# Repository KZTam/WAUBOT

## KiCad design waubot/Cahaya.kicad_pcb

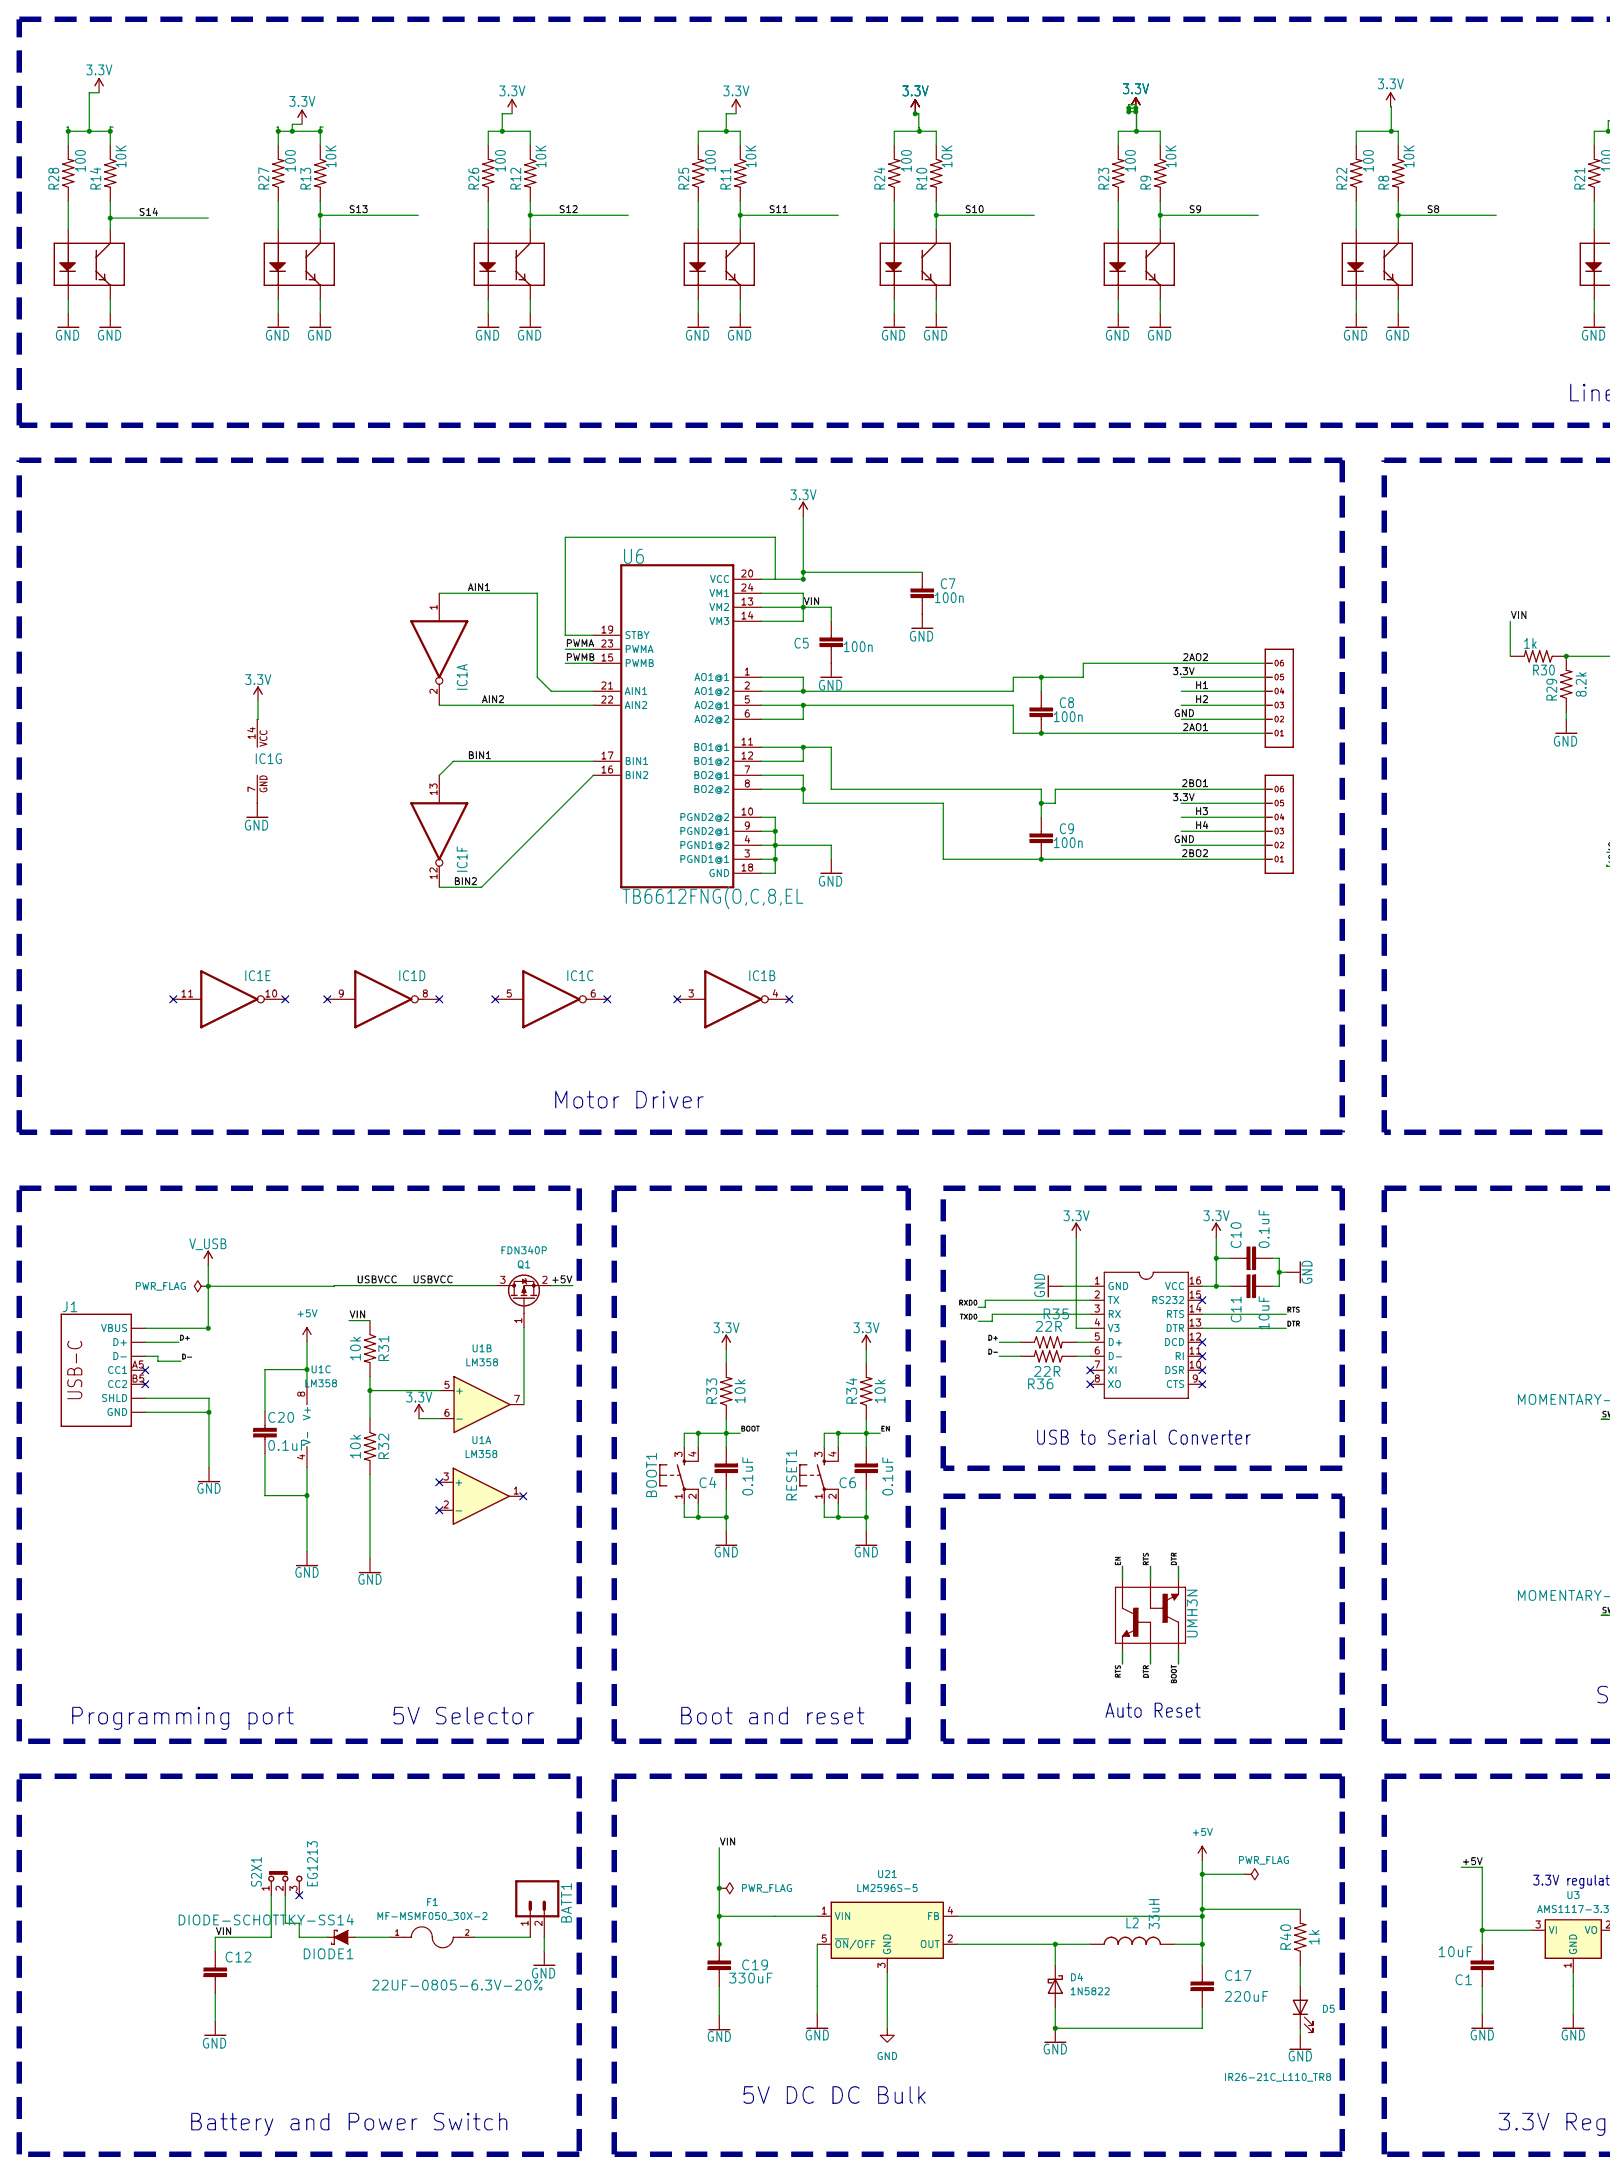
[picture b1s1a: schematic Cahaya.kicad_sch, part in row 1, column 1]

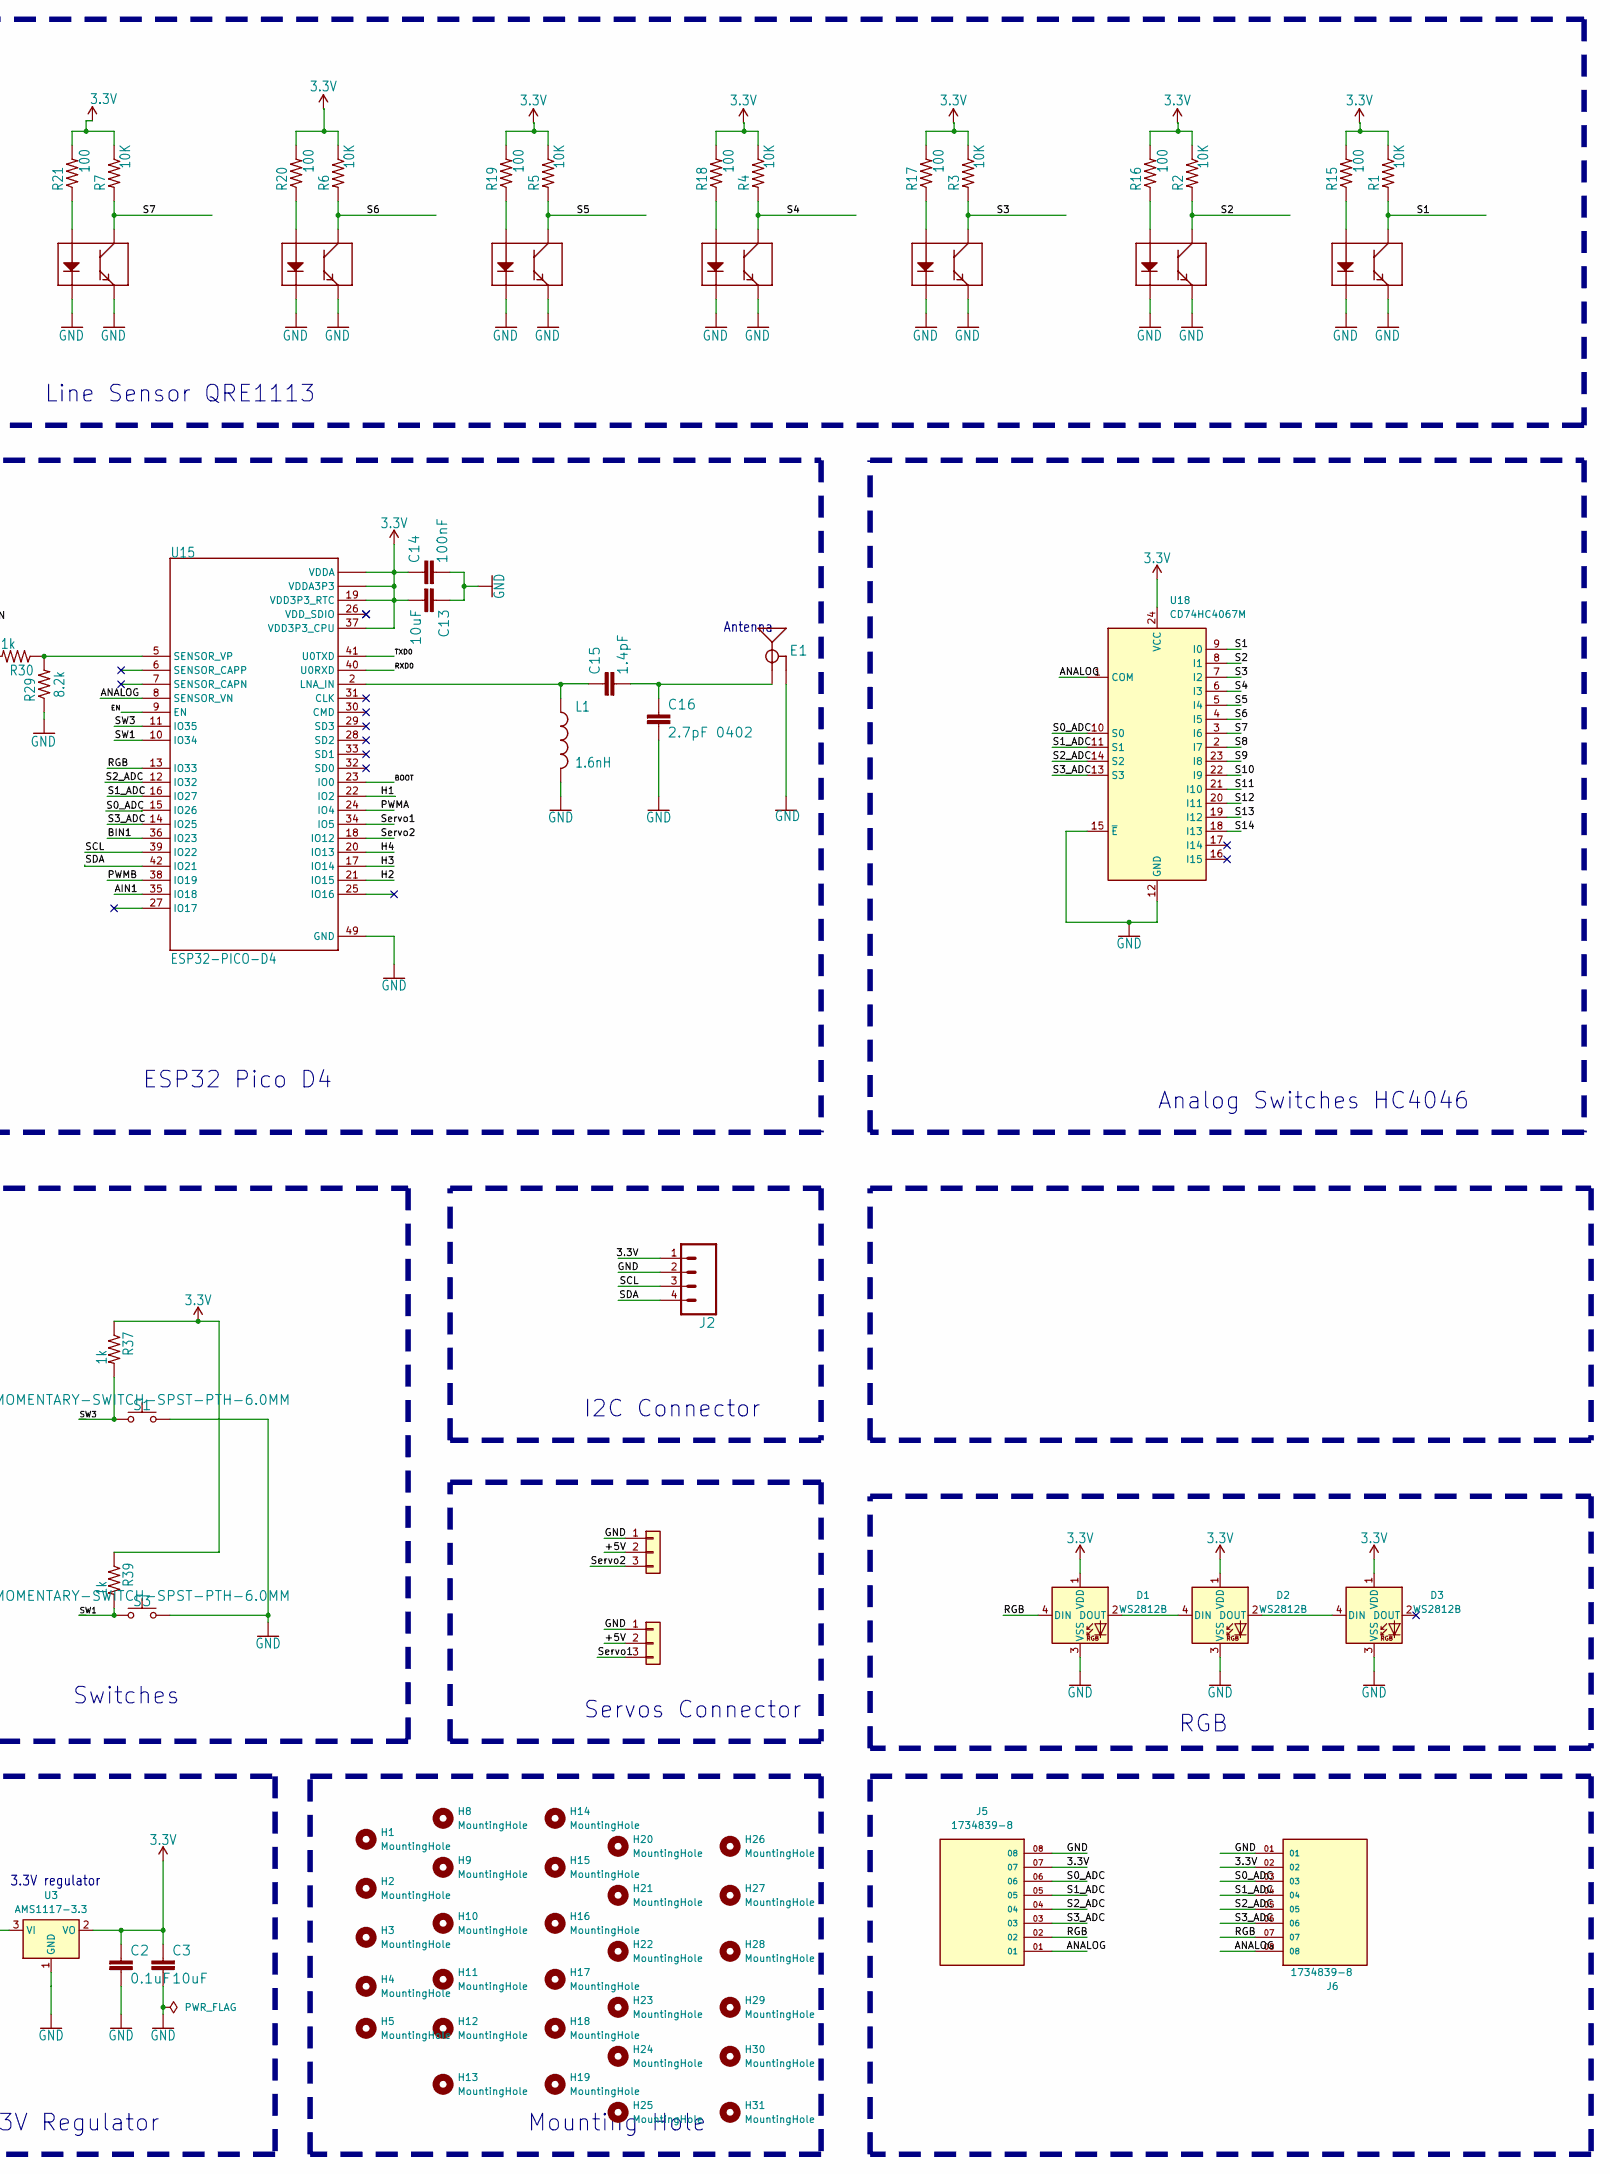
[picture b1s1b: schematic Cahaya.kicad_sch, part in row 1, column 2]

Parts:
BATT1: CONN_02; TerminalBlock_4Ucon_1x02_P3.50mm_Horizontal
BOOT1: MOMENTARY-SWITCH-SPST-2-SMD-4.6X2.8MM; TACTILE_SWITCH_SMD_4.6X2.8MM
C1, C3, C11, C13: 10uF; C0603
C2, C4, C6, C10, C20: 0.1uF; C0603
C5, C7, C8, C9: 100n; C0603-ROUND
C12: 22UF-0805-6.3V-20%; 0805
C14: 100nF; C0603
C15: 1.4pF; 0402
C16: 2.7pF 0402; C0402
C17: 220uF; CP_Elec_8x10.5
C19: 330uF; CP_Elec_8x10.5
D1, D2, D3: WS2812B; LED_WS2812B_PLCC4_5.0x5.0mm_P3.2mm
D4: 1N5822; D_SMA
D5: IR26-21C_L110_TR8; LED_1206_3216Metric
DIODE1: DIODE-SCHOTTKY-SS14; SMA-DIODE
E1: ANTENNA-GROUNDEDTRACE-15.2MM; TRACE_ANTENNA_2.4GHZ_15.2MM
F1: MF-MSMF050_30X-2; FUSER_MF-MSMF050_30X-2
H1, H2, H3, H4, H5, H8, H9, H10, H11, H12, H13, H14, H15, H16, H17, H18, H19, H20, H21, H22, H23, H24, H25, H26, H27, H28, H29, H30, H31: MountingHole; MountingHole_3.2mm_M3
IC1: 7404D; SO14
J1: USB_C16PIN; USB-C-16P
J2: CONN_04PTH; MODULE_DM-OLED096-636
J3, J4: Conn_01x03; 1X03
J5, J6: 1734839-8; SAMTEC_ZF5S-08-01-T-WT; VOLTAGE 250V; PARTREV C
L1: 1.6nH; L0402
L2: 33uH; L_12x12mm_H6mm
MOTOR1: 1X6; JST_XA_B06B-XASK-1-A_1x06_P2.50mm_Vertical
MOTOR2: 1X6; JST_XA_B06B-XASK-1_1x06_P2.50mm_Vertical
Q1: FDN340P; SOT-23
Q2: UMH3N; UMH3NTN
R1, R2, R3, R4, R5, R6, R7, R8, R9, R10, R11, R12, R13, R14: 10K; 0603-RES
R15, R16, R17, R18, R19, R20, R21, R22, R23, R24, R25, R26, R27, R28: 100; 0603-RES
R29: 8.2k; 0603-RES
R30, R37, R39: 1k; 0603-RES
R31, R32, R33, R34: 10k; R0603
R35, R36: 22R; R0603
R40: 1k; R0603
RESET1: MOMENTARY-SWITCH-SPST-2-SMD-4.6X2.8MM; TACTILE_SWITCH_SMD_4.6X2.8MM
S1, S3: MOMENTARY-SWITCH-SPST-PTH-6.0MM; soft button
S2X1: EG1213
U1: LM358; SOIC-8_3.9x4.9mm_P1.27mm
U2, U4, U5, U7, U8, U10, U11, U12, U13, U14, U16, U17, U19, U20: QRE11131:1; QRE1113-1_1
U3: AMS1117-3.3; SOT-223-3_TabPin2
U6: TB6612FNG(O,C,8,EL; SOP65P760X160-24N
U9: CH340G; SOIC16
U15: ESP32-PICO-D4; PQFN50P700X700X104-49N
U18: CD74HC4067M; SOIC-24W_7.5x15.4mm_P1.27mm
U21: LM2596S-5; TO-263-5_TabPin3

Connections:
3.3V: C2.1, C3.2, C7.2, C10.1, C11.1, C13.2, C14.1, D1.1 (VDD), D2.1 (VDD), D3.1 (VDD), IC1.14 (VCC), J2.1, J5.07, J6.02, MOTOR1.5, MOTOR2.5, R1.1, R2.1, R3.1, R4.1, R5.1, R6.1, R7.1, R8.1, R9.1, R10.1, R11.1, R12.1, R13.1, R14.1, R15.2, R16.2, R17.2, R18.2, R19.2, R20.2, R21.2, R22.2, R23.2, R24.2, R25.2, R26.2, R27.2, R28.2, R33.2, R34.2, R37.1, R39.1, U1.6 (-), U3.2 (VO), U6.19 (STBY), U6.20 (VCC), U9.4 (V3), U9.16 (VCC), U15.1 (VDDA), U15.3 (VDDA3P3), U15.4 (VDDA3P3), U15.19 (VDD3P3_RTC), U15.37 (VDD3P3_CPU), U15.43 (VDDA), U15.46 (VDDA), U18.24 (VCC)
+5V: C1.2, C17.1, C20.1, J3.2, J4.2, L2.2, Q1.2 (S), R40.2, U1.8 (V+), U3.3 (VI), U21.4 (FB)
/2AO1: C8.1, MOTOR1.1, U6.5 (AO2@1), U6.6 (AO2@2)
/2AO2: C8.2, MOTOR1.6, U6.1 (AO1@1), U6.2 (AO1@2)
/2BO1: C9.2, MOTOR2.6, U6.11 (BO1@1), U6.12 (BO1@2)
/2BO2: C9.1, MOTOR2.1, U6.7 (BO2@1), U6.8 (BO2@2)
/AIN1: IC1.1 (I), U6.21 (AIN1), U15.35 (IO18)
/AIN2: IC1.2 (O), U6.22 (AIN2)
/ANALOG: J5.01, J6.08, U15.8 (SENSOR_VN), U18.1 (COM)
/BIN1: IC1.13 (I), U6.17 (BIN1), U15.36 (IO23)
/BIN2: IC1.12 (O), U6.16 (BIN2)
/BOOT: BOOT1.3, BOOT1.4, C4.2, Q2.3, R33.1, U15.23 (IO0)
/D+: J1.A6 (D+), J1.B6 (D+), R35.1
/D-: J1.A7 (D-), J1.B7 (D-), R36.2
/DTR: Q2.2, Q2.4, U9.13 (DTR)
/EN: C6.2, Q2.6, R34.1, RESET1.3, RESET1.4, U15.9 (EN)
/H1: MOTOR1.4, U15.22 (IO2)
/H2: MOTOR1.3, U15.21 (IO15)
/H3: MOTOR2.4, U15.17 (IO14)
/H4: MOTOR2.3, U15.20 (IO13)
/PWMA: U6.23 (PWMA), U15.24 (IO4)
/PWMB: U6.15 (PWMB), U15.38 (IO19)
/RGB: D1.4 (DIN), J5.02, J6.07, U15.13 (IO33)
/RTS: Q2.1, Q2.5, U9.14 (RTS)
/RXD0: U9.2 (TX), U15.40 (U0RXD)
/S0_ADC: J5.06, J6.03, U15.15 (IO26), U18.10 (S0)
/S1: R1.2, U18.9 (I0), U19.3 (C)
/S1_ADC: J5.05, J6.04, U15.16 (IO27), U18.11 (S1)
/S2: R2.2, U17.3 (C), U18.8 (I1)
/S2_ADC: J5.04, J6.05, U15.12 (IO32), U18.14 (S2)
/S3: R3.2, U16.3 (C), U18.7 (I2)
/S3_ADC: J5.03, J6.06, U15.14 (IO25), U18.13 (S3)
/S4: R4.2, U14.3 (C), U18.6 (I3)
/S5: R5.2, U13.3 (C), U18.5 (I4)
/S6: R6.2, U12.3 (C), U18.4 (I5)
/S7: R7.2, U11.3 (C), U18.3 (I6)
/S8: R8.2, U10.3 (C), U18.2 (I7)
/S9: R9.2, U8.3 (C), U18.23 (I8)
/S10: R10.2, U7.3 (C), U18.22 (I9)
/S11: R11.2, U5.3 (C), U18.21 (I10)
/S12: R12.2, U4.3 (C), U18.20 (I11)
/S13: R13.2, U2.3 (C), U18.19 (I12)
/S14: R14.2, U18.18 (I13), U20.3 (C)
/SCL: J2.3, U15.39 (IO22)
/SDA: J2.4, U15.42 (IO21)
/SW1: R39.2, S3.1, U15.10 (IO34)
/SW3: R37.2, S1.1, U15.11 (IO35)
/Servo1: J4.3, U15.34 (IO5)
/Servo2: J3.3, U15.18 (IO12)
/TXD0: U9.3 (RX), U15.41 (U0TXD)
/VIN: C5.2, C12.1, C19.1, R30.2, R31.1, S2X1.1, U6.13 (VM2), U6.14 (VM3), U6.24 (VM1), U21.1 (VIN)
GND: BATT1.2, BOOT1.1, BOOT1.2, C1.1, C2.2, C3.1, C4.1, C5.1, C6.1, C7.1, C10.2, C11.2, C12.2, C13.1, C14.2, C16.2, C17.2, C19.2, C20.2, D1.3 (VSS), D2.3 (VSS), D3.3 (VSS), D4.2 (A), D5.1 (K), E1.GND, IC1.7 (GND), J1.GND, J1.GND2 (GND), J1.SHLD1 (SHLD), J1.SHLD2 (SHLD), J1.SHLD3 (SHLD), J1.SHLD4 (SHLD), J1.SHLD5 (SHLD), J1.SHLD6 (SHLD), J1.SHLD7 (SHLD), J1.SHLD8 (SHLD), J2.2, J3.1, J4.1, J5.08, J6.01, L1.2, MOTOR1.2, MOTOR2.2, R29.1, R32.2, RESET1.1, RESET1.2, S1.2, S3.2, U1.4 (V-), U2.2 (K), U2.4 (E), U3.1 (GND), U4.2 (K), U4.4 (E), U5.2 (K), U5.4 (E), U6.3 (PGND1@1), U6.4 (PGND1@2), U6.9 (PGND2@1), U6.10 (PGND2@2), U6.18 (GND), U7.2 (K), U7.4 (E), U8.2 (K), U8.4 (E), U9.1 (GND), U10.2 (K), U10.4 (E), U11.2 (K), U11.4 (E), U12.2 (K), U12.4 (E), U13.2 (K), U13.4 (E), U14.2 (K), U14.4 (E), U15.49 (GND), U16.2 (K), U16.4 (E), U17.2 (K), U17.4 (E), U18.12 (GND), U18.15 (~E), U19.2 (K), U19.4 (E), U20.2 (K), U20.4 (E), U21.3 (GND), U21.5 (~ON/OFF)
unnamed: BATT1.1, F1.2
unnamed: D1.2 (DOUT), D2.4 (DIN)
unnamed: D2.2 (DOUT), D3.4 (DIN)
unnamed: D4.1 (K), L2.1, U21.2 (OUT)
unnamed: D5.2 (A), R40.1
unnamed: DIODE1.A, F1.1
unnamed: DIODE1.C, S2X1.2
unnamed: C15.2, C16.1, E1.ANT (SIGNAL)
unnamed: Q1.1 (G), U1.7
unnamed: R31.2, R32.1, U1.5 (+)
unnamed: R27.1, U2.1 (A)
unnamed: R26.1, U4.1 (A)
unnamed: R25.1, U5.1 (A)
unnamed: R24.1, U7.1 (A)
unnamed: R23.1, U8.1 (A)
unnamed: R35.2, U9.5 (D+)
unnamed: R36.1, U9.6 (D-)
unnamed: R22.1, U10.1 (A)
unnamed: R21.1, U11.1 (A)
unnamed: R20.1, U12.1 (A)
unnamed: R19.1, U13.1 (A)
unnamed: R18.1, U14.1 (A)
unnamed: C15.1, L1.1, U15.2 (LNA_IN)
unnamed: R29.2, R30.1, U15.5 (SENSOR_VP)
unnamed: R17.1, U16.1 (A)
unnamed: R16.1, U17.1 (A)
unnamed: R15.1, U19.1 (A)
unnamed: R28.1, U20.1 (A)
V_USB: J1.VBUS1 (VBUS), J1.VBUS2 (VBUS), Q1.3 (D)

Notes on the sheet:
Line Sensor QRE1113
5V Selector
Antenna
Auto Reset
ESP32 Pico D4
RGB
Programming port
Servos Connector
5V DC DC Bulk
3.3V regulator
Battery and Power Switch
I2C Connector
Motor Driver
Analog Switches HC4046
3.3V Regulator
Mounting Hole
Switches
USB to Serial Converter
Boot and reset

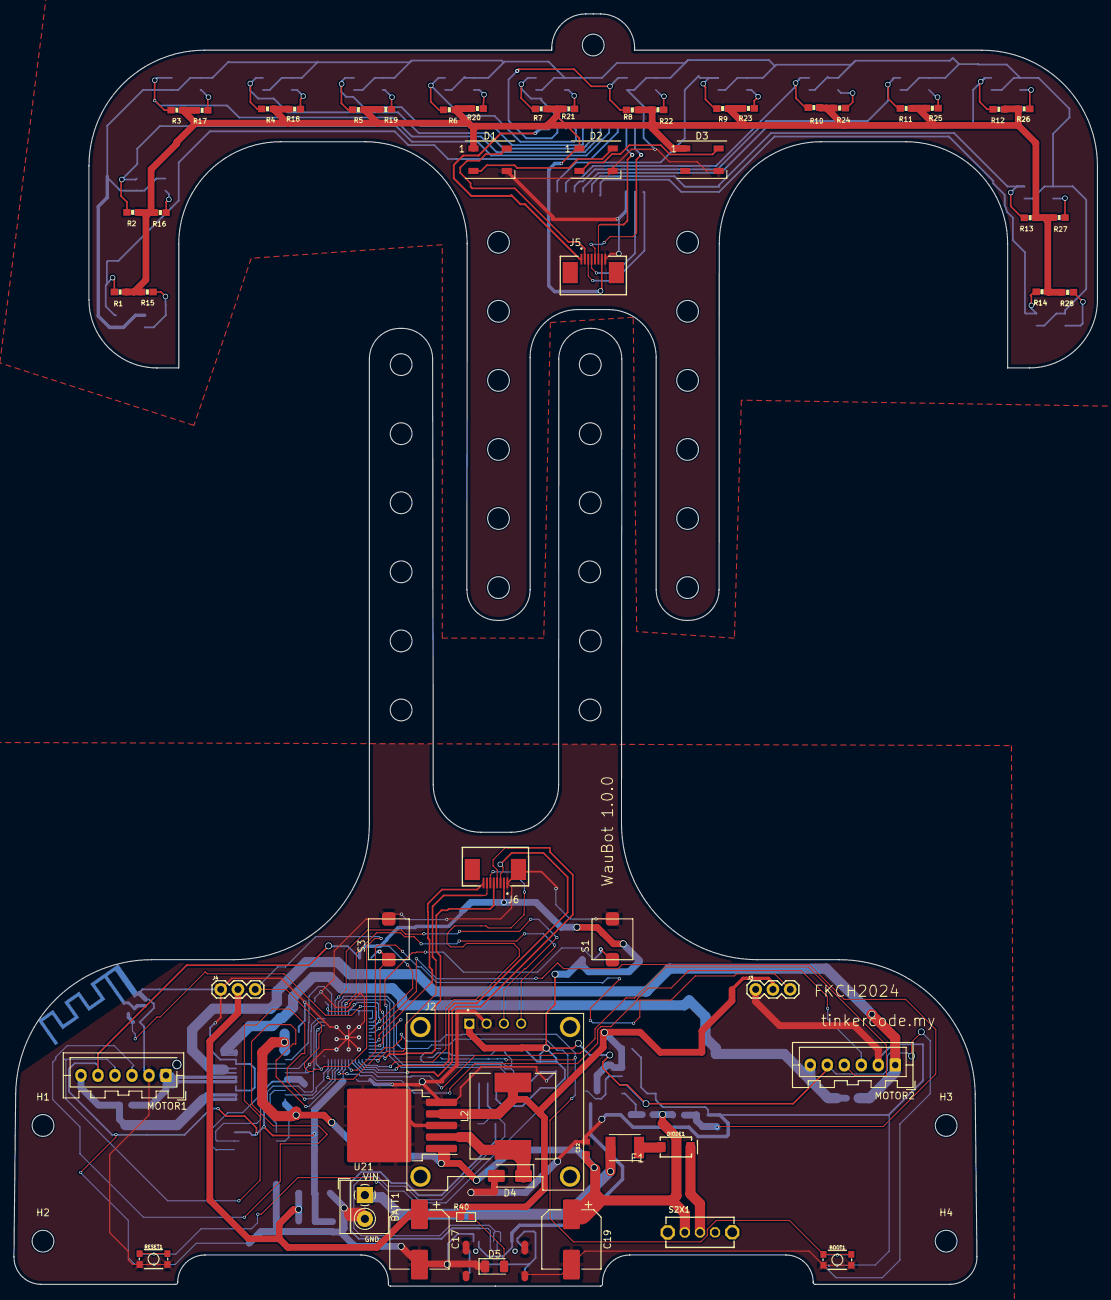
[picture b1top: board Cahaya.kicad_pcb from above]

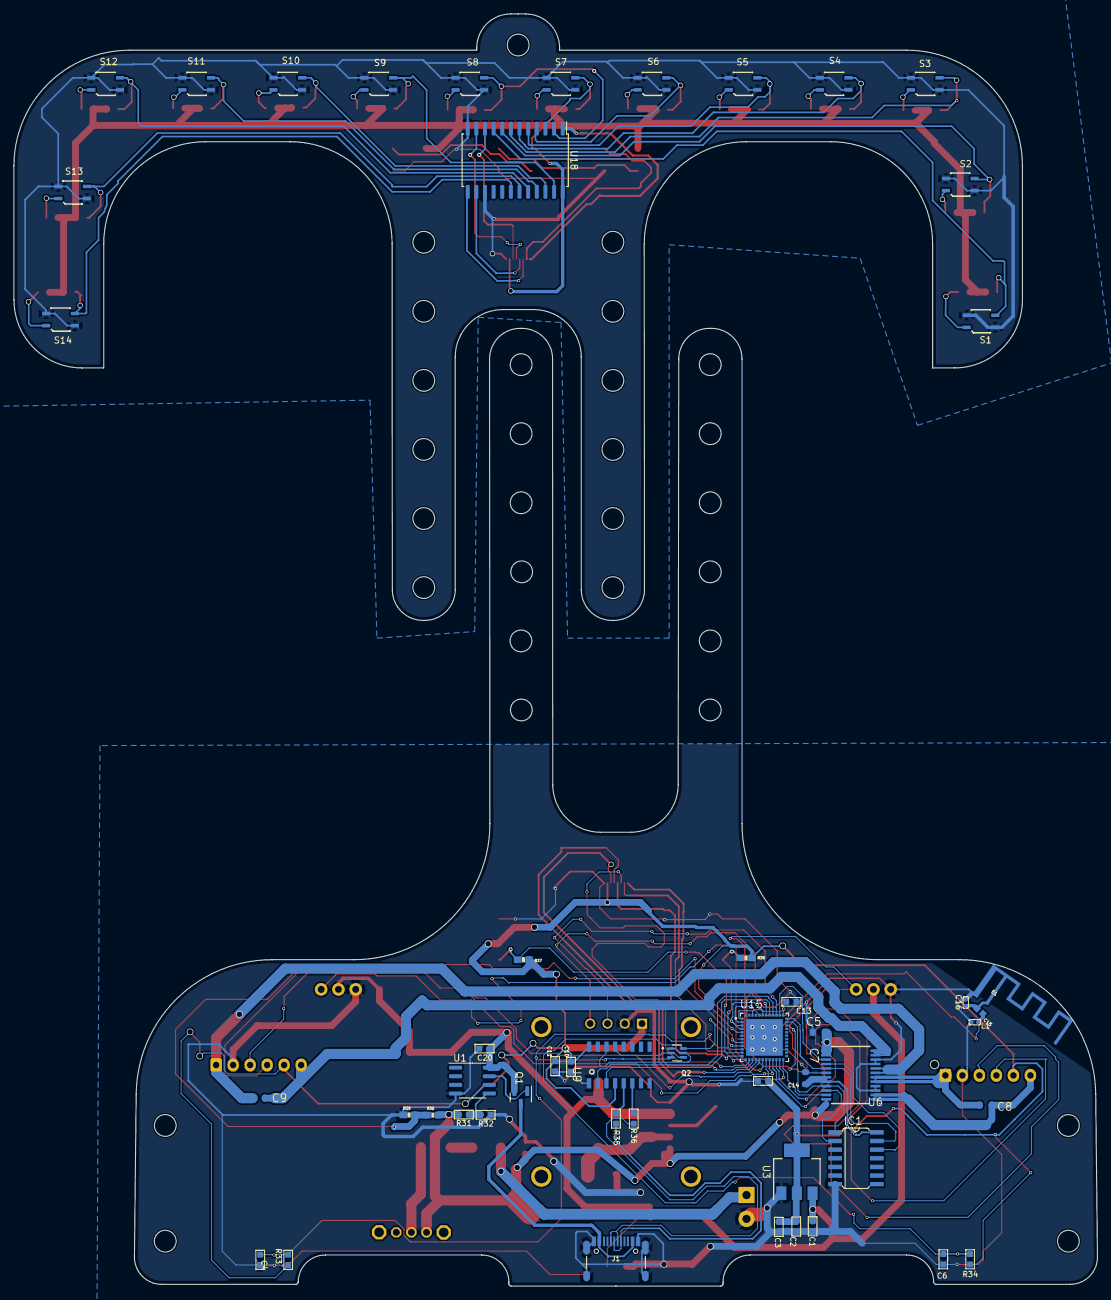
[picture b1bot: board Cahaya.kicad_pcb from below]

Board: 2 copper layers, 159.4 x 187.1 mm, 135 parts (52 on the bottom side), 81 nets.
